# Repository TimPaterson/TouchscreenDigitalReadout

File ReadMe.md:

# Smart Touchscreen DRO for Milling Machines
__As seen in this article in [*Servo* magazine](https://www.timpaterson.com/articles/Servo/SmartDroP1_P2.pdf)!__

### Introduction
The Smart DRO is a touchscreen digital readout for milling machines. You 
can see in the photos an installation on a Grizzly mill/drill, replacing 
the original display head (shown on the mill table). The OEM position 
sensors for the X, Y, and Z axes directly connect to the back of the unit.
Position sensors like these are individually available commercially for 
mills that do not have them factory installed.

The Smart DRO can greatly simplify milling from dimensioned drawings. If 
you enter the diameter of the tool it can automatically adjust the
display reading by the tool radius. This allows you to cut at the specified 
dimension without having to add or subtract the radius offset. Note in the 
lower left corner of the main screen (the dark rectangle with a circle on 
each side): you can select which side you're cutting so it knows whether to
add or subtract the cutter radius.

You can enter the diameter of each tool as you use it, but the Smart DRO
can also keep your entire tool library (up to 500 tools) in non-volatile
memory. You can enter the list manually or import it from a flash drive
if you share it with other programs or devices. The Smart DRO will also
calculate feeds and speeds, and it displays the current feed rate when
any of the axes move.

Another helpful feature is the undo list for changes in the origin of any
axis. If you accidently zero out or set a value to the wrong axis, you can
easily recover the origin even if the axis has been moved.

The on-screen calculator allows you to include axis readings in 
calculations, and copy results back to an axis.

### Sensor Compatibility
It is industry standard that position sensors use a 9-pin "D" connector
(like a PC serial port). However, there is no standard for the pin
assignments for the connector! To solve this, the Smart DRO uses a pinout
adapter for each axis. A tiny printed circuit board with a single connector
routes signals to the correct pins. A set of 3 of these PCBs costs just 45 cents.
See the [*Servo* magazine article](https://www.timpaterson.com/articles/Servo/SmartDroP1_P2.pdf)
for more info.

### The Project
The main component is the 10" LCD touchscreen, specified in the parts 
list. This repository includes all other aspects of the hardware design 
needed to build this project as shown. These elements include:
- Custom [electronics design](https://github.com/TimPaterson/TouchscreenDigitalReadout/tree/master/Electronics),
with printed circuit board ready for fabrication.
- Enclosure design, using a 3D-printed bezel and machined aluminum back.

A [separate repository](https://github.com/TimPaterson/Touchscreen-DRO-Firmware) 
has the microcontroller firmware and graphics images.

Here are the critical links:
- The [*Servo* magazine article](https://www.timpaterson.com/articles/Servo/SmartDroP1_P2.pdf)
has complete instructions on how to build it.
- The [Touchscreen-DRO-Firmware](https://github.com/TimPaterson/Touchscreen-DRO-Firmware) repository
has firmware and everything else you need, bundled into a release.
- [Touchscreen at BuyDisplay.com](https://www.buydisplay.com/serial-spi-i2c-10-1-inch-tft-lcd-module-dislay-w-ra8876-optl-touch-panel).
Be sure to select options per the [parts list](https://github.com/TimPaterson/TouchscreenDigitalReadout/blob/master/Electronics/DroPartsList.pdf).
- [Main PCB shared at OSH Park](https://oshpark.com/shared_projects/AQX5MSFg). The
EAGLE CAD for the PCB is included is you want to use another PCB source.
- Pinout PCBs at OSH Park. Pinouts are specified by a 4-digit number where
the digits are the pin numbers on the 9-pin D-connector for GND, +5V, A, & B, respectively.
  - [2768 (Grizzly)](https://oshpark.com/shared_projects/TLEyl9I6)
  - [2134 (Jing/Jcgs)](https://oshpark.com/shared_projects/ilViDS0E)
  - [6724 (Acu-Rite)](https://oshpark.com/shared_projects/GIDBOB83)
- [Tool Library Manager](https://github.com/TimPaterson/CNC-Tool-Library-Manager)
for making tool libary files the Smart DRO can import.

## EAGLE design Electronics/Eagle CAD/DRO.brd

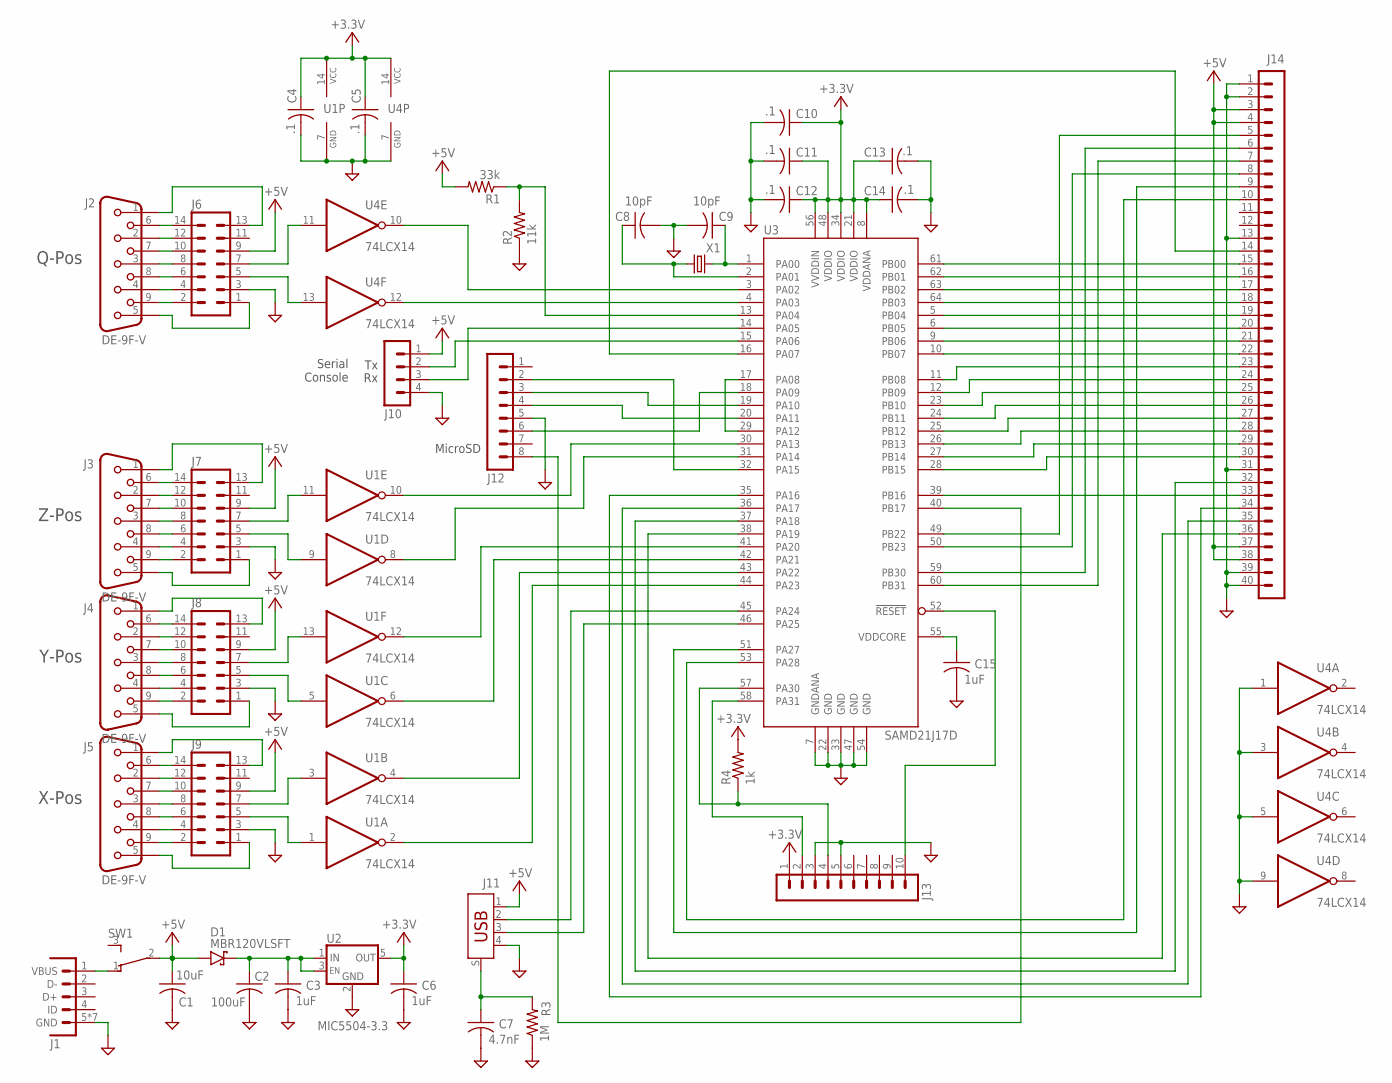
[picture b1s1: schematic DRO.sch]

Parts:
C1: 10uF; 0603
C2: 100uF; C1206
C3, C6, C15: 1uF; 0603
C4, C5, C10, C11, C12, C13, C14: .1; 0603
C7: 4.7nF; 0603
C8, C9: 10pF; 0603
D1: MBR120VLSFT; SOD123
J1: USB_MINI-B-MICRO-B_FCI; USB_MICRO-B_FCI
J2, J3, J4, J5: DE-9F-V; DE-9F-PCB-VERT
J6, J7, J8, J9: CONN-14-BIDI; CONN-1.27X2-14
J10: CONN-4-2.54X1-RA; CONN-2.54X1-4-RA
J11: USB-A-SHIELD; USB-A
J12: CONN-8-2.54X2; CONN-2.54X2-8
J13: CONN-10-ARM; CONN-1.27X2-10
J14: CONN-40; CONN-2.54X2-40
R1: 33k; 0603
R2: 11k; 0603
R3: 1M; 0603
R4: 1k; 0603
SW1: SWITCH-SPDT-MINI-RA-SHORT
U1, U4: 74LCX14; TSSOP14
U2: MIC5504-3.3; SOT23-5
U3: SAMD21J17D; TQFP64-0.5
X1: CRYSTAL-3X1.5; XTAL-SMD-3.2X1.5-2PIN

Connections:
+3.3V: C4.1, C5.1, C6.1, C10.1, C11.1, C12.1, C13.1, C14.1, J13.1, R4.2, U1.14 (VCC), U2.5 (OUT), U3.8 (VDDANA), U3.21 (VDDIO), U3.34 (VDDIO), U3.48 (VDDIO), U3.56 (VVDDIN), U4.14 (VCC)
+5V: C1.1, D1.A, J6.9, J7.9, J8.9, J9.9, J10.1, J11.1, J14.3, J14.4, J14.37, J14.38, R1.2, SW1.2 (C)
GND: C1.2, C2.2, C3.2, C4.2, C5.2, C6.2, C7.2, C8.2, C9.2, C10.2, C11.2, C12.2, C13.2, C14.2, C15.2, J1.5 (GND), J1.SHELL1 (GND), J1.SHELL2 (GND), J1.SHELL3 (GND), J1.SHELL4 (GND), J1.SHELL5 (GND), J1.SHELL6 (GND), J6.3, J7.3, J8.3, J9.3, J10.4, J11.4, J12.5, J13.3, J13.5, J14.1, J14.2, J14.13, J14.31, J14.39, J14.40, R2.1, R3.1, U1.7 (GND), U2.2 (GND), U3.7 (GNDANA), U3.22 (GND), U3.33 (GND), U3.47 (GND), U3.54 (GND), U4.1 (I), U4.3 (I), U4.5 (I), U4.7 (GND), U4.9 (I)
J1: J14.17, U3.63 (PB02)
unnamed: J14.15, U3.61 (PB00)
unnamed: J14.22, U3.10 (PB07)
unnamed: J14.23, U3.11 (PB08)
unnamed: J14.24, U3.12 (PB09)
unnamed: J14.25, U3.23 (PB10)
unnamed: J14.26, U3.24 (PB11)
unnamed: J14.27, U3.25 (PB12)
unnamed: J14.28, U3.26 (PB13)
unnamed: J14.29, U3.27 (PB14)
unnamed: J14.30, U3.28 (PB15)
unnamed: J14.16, U3.62 (PB01)
unnamed: J11.2, U3.45 (PA24)
unnamed: J14.18, U3.64 (PB03)
unnamed: J14.19, U3.5 (PB04)
unnamed: J14.20, U3.6 (PB05)
unnamed: J14.21, U3.9 (PB06)
unnamed: J11.3, U3.46 (PA25)
unnamed: U3.17 (PA08), U3.29 (PA12)
unnamed: R1.1, R2.2, U3.13 (PA04)
unnamed: C9.1, U3.1 (PA00), X1.2
unnamed: C8.1, U3.2 (PA01), X1.1
unnamed: C2.1, C3.1, D1.C, U2.1 (IN), U2.3 (EN)
unnamed: J13.2, U3.58 (PA31)
unnamed: C15.1, U3.55 (VDDCORE)
unnamed: J13.4, R4.1, U3.57 (PA30)
unnamed: J14.33, U3.39 (PB16)
unnamed: J13.10, U3.52 (!RESET)
unnamed: J14.5, U3.49 (PB22)
unnamed: J14.8, U3.50 (PB23)
unnamed: J14.6, U3.59 (PB30)
unnamed: J14.7, U3.60 (PB31)
unnamed: J14.10, U3.53 (PA28)
unnamed: J14.9, U3.51 (PA27)
unnamed: J14.36, U3.38 (PA19)
unnamed: J14.32, U3.37 (PA18)
unnamed: J14.35, U3.36 (PA17)
unnamed: J14.34, U3.35 (PA16)
unnamed: J12.3, U3.19 (PA10)
unnamed: J14.14, U3.16 (PA07)
unnamed: J12.6, U3.18 (PA09)
unnamed: J12.4, U3.20 (PA11)
unnamed: J12.2, U3.32 (PA15)
unnamed: U1.10 (O), U3.30 (PA13)
unnamed: J10.3, U3.14 (PA05)
unnamed: J10.2, U3.15 (PA06)
unnamed: U3.4 (PA03), U4.12 (O)
unnamed: U3.3 (PA02), U4.10 (O)
unnamed: J12.8, U3.40 (PB17)
unnamed: U1.8 (O), U3.31 (PA14)
unnamed: U1.2 (O), U3.44 (PA23)
unnamed: U1.4 (O), U3.43 (PA22)
unnamed: U1.6 (O), U3.42 (PA21)
unnamed: U1.12 (O), U3.41 (PA20)
unnamed: J6.7, U4.11 (I)
unnamed: J6.5, U4.13 (I)
unnamed: J2.5, J6.1
unnamed: J2.9, J6.2
unnamed: J2.4, J6.4
unnamed: J2.8, J6.6
unnamed: J2.3, J6.8
unnamed: J2.7, J6.10
unnamed: J2.2, J6.12
unnamed: J2.6, J6.14
unnamed: J2.1, J6.13
unnamed: J7.5, U1.9 (I)
unnamed: J8.5, U1.5 (I)
unnamed: J9.5, U1.1 (I)
unnamed: J9.7, U1.3 (I)
unnamed: J8.7, U1.13 (I)
unnamed: J7.7, U1.11 (I)
unnamed: J3.6, J7.14
unnamed: J3.2, J7.12
unnamed: J3.7, J7.10
unnamed: J3.3, J7.8
unnamed: J3.8, J7.6
unnamed: J3.4, J7.4
unnamed: J3.9, J7.2
unnamed: J4.6, J8.14
unnamed: J4.2, J8.12
unnamed: J4.7, J8.10
unnamed: J4.3, J8.8
unnamed: J4.8, J8.6
unnamed: J4.4, J8.4
unnamed: J4.9, J8.2
unnamed: J5.6, J9.14
unnamed: J5.2, J9.12
unnamed: J5.7, J9.10
unnamed: J5.3, J9.8
unnamed: J5.8, J9.6
unnamed: J5.4, J9.4
unnamed: J5.9, J9.2
unnamed: J3.1, J7.13
unnamed: J3.5, J7.1
unnamed: J4.1, J8.13
unnamed: J5.1, J9.13
unnamed: J4.5, J8.1
unnamed: J5.5, J9.1
unnamed: C7.1, J11.S (SHIELD), R3.2
VBUS: J1.1 (VBUS), SW1.1 (NC)

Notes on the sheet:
Serial Console
MicroSD
Q-Pos
Z-Pos
Y-Pos
X-Pos

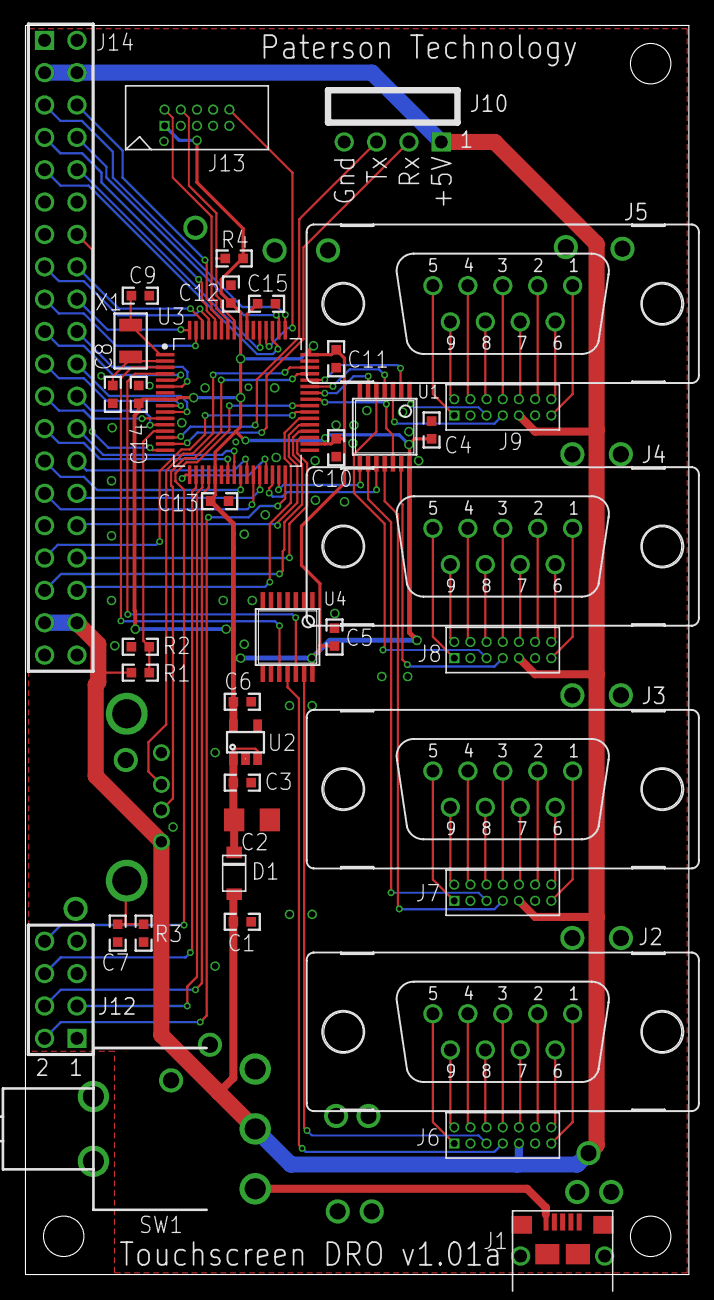
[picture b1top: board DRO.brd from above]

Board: 2 copper layers, 52.1 x 98.0 mm, 40 parts (1 on the bottom side), 103 nets.

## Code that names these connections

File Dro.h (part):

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//*********************************************************************
// Define port pins
//
// PA00 - xtal
// PA01 - xtal
// PA02 - in, Q position A (EXINT 2)
// PA03 - in, Q position B (EXINT 3)
// PA04 - analog in, supply voltage (AC AIN[0])
// PA05 - in, console serial RX data (SERCOM 0 pad 1)
// PA06 - out, console serial TX data (SERCOM 0 pad 2)
// PA07 - out, backlight PWM (TCC1 WO[1])
// PA08 - in, supply low (NMI)
// PA09 - in, MicroSD DOUT/MISO (SERCOM 2 pad 1 & EXINT 9)
// PA10 - out, MicroSD DIN/MOSI (SERCOM 2 pad 2)
// PA11 - out, MicroSD SCK (SERCOM 2 pad 3)
// PA12 - out, supply low (analog comparator CMP[0])
// PA13 - in, Z position A (EXINT 13)
// PA14 - in, Z position B (EXINT 14)
// PA15 - out, MicroSD CS
// PA16 - out, RTP DIN/MOSI (SERCOM 1 pad 0)
// PA17 - out, RTP SCK (SERCOM 1 pad 1)
// PA18 - out, RTP CS
// PA19 - in, RTP DOUT/MISO (SERCOM 1 pad 3)
// PA20 - in, Y position A (EXINT 4)
// PA21 - in, Y position B (EXINT 5)
// PA22 - in, X position A (EXINT 6)
// PA23 - in, X position B (EXINT 7)
// PA24 - USB D-
// PA25 - USB D+
// PA27 - in, RA8876 WAIT (EXINT 15)
// PA28 - in, RA8876 INT (EXINT 8)
//
// PB00 - in/out, RA8876 DB0
// PB01 - in/out, RA8876 DB1
// PB02 - in/out, RA8876 DB2
// PB03 - in/out, RA8876 DB3
// PB04 - in/out, RA8876 DB4
// PB05 - in/out, RA8876 DB5
// PB06 - in/out, RA8876 DB6
// PB07 - in/out, RA8876 DB7
// PB08 - in/out, RA8876 DB8
// PB09 - in/out, RA8876 DB9
// PB10 - in/out, RA8876 DB10
// PB11 - in/out, RA8876 DB11
// PB12 - in/out, RA8876 DB12
// PB13 - in/out, RA8876 DB13
// PB14 - in/out, RA8876 DB14
// PB15 - in/out, RA8876 DB15
// PB16 - in w/pull-up, RTP IRQ (EXINT 0)
// PB17 - in, MicroSD card detect (EXINT 1)
// PB22 - out, RA8876 E (TC7 WO[0])
// PB23 - out, RA8876 C/D
// PB30 - out, RA8877 R/W
// PB31 - out, RA9977 CS

enum PortAbitMap
{
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
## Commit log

2020-10-15 Successfully read mill position sensor
2020-10-18 LCD controller initialization partially complete
2020-10-18 remove .vs folder
2020-10-21 LCD test pattern displays, touch data working
2020-10-23 Success drawing rectangle and display text w/internal font
2020-10-23 Success writing text with external font
2020-10-25 Program serial flash through SPI
2020-10-26 Use printf() to write text to LCD
2020-10-27 Touch logic now reporting screen coordinates
2020-10-28 Target cursor follows touch
2020-11-07 Display keypad and detect touching its keys
2020-11-08 USB mouse working
2020-11-12 Add FAT file system with SD card driver, untested
2020-11-18 FAT file system successfully enumerates root folder on SD card
2020-11-19 Enable parameters to be stored in EEPROM
2020-11-23 Add touch screen calibration, saving result to EEPROM
2020-11-24 Successfully display full screen image from microSD card
2020-12-01 Canvas & TextDisplay classes; success writing string to screen with generated font.
2020-12-15 Main screen image now copied from serial flash
2020-12-17 Text output working again
2020-12-17 TextField and new TextLine support printf
2020-12-18 Get PIP working
2020-12-20 All axis displays show correct position.
2020-12-23 add & implement abs/inc and inch/mm toggle buttons
2020-12-24 add functions to add/remove selection borders
2020-12-26 Figure out text cursor
2020-12-29 Calculator keypad seems fully functional
2020-12-31 Use colors exported by Screen Designer
2021-01-04 Success with display directory and file read on USB flash drive
2021-01-05 Automatically mount SD card or USB flash drive when present
2021-01-07 Implement calculator memories
2021-01-08 Add mouse pointer image; mouse functions same as touch
2021-01-13 Add tool offset and speed/feed display to screen and implement in code
2021-01-19 Create and fully implement settings screen
2021-01-20 Add choice of two orientations of coordinate system
2021-01-20 Save Settings to EEPROM on exit
2021-01-21 Fix PIP hit testing; separate width from stride
2021-01-26 Successful test of list scrolling
2021-01-28 +/- key operates on current value
2021-01-30 Add and display tool library image
2021-01-30 Use image arrays to select image from list
2021-01-31 Refactor tool display, adding ToolLib.h
2021-02-02 ToolLib now handles single tool display
2021-02-04 Manual entry into tool library working
2021-02-06 Final keyboard layouts; import tool library from flash drive
2021-02-07 More tool library functionality: select from list, delete
2021-02-07 Use references instead of pointers on TextField constructors
2021-02-11 Enter/edit tool description w/on-screen keyboard
2021-02-19 Successfully browsing flash drive with list box
2021-02-19 Add Hard Fault handler in Debug mode
2021-02-19 Switch to 16-bit fonts
2021-02-23 Tool library import/export dialog mostly working
2021-02-25 Real-time clock and file timestamps working
2021-02-25 Reorganize ArmLib & Dro folder structures
2021-02-28 Error handling for tool library file operations
2021-02-28 Use image for scroll thumb
2021-03-02 Finish multi-drive support and file error handling
2021-03-02 Add horizontal scrolling to EditLine
2021-03-03 USB keyboard can enter data into edit box
2021-03-04 Add icon to delete content of edit box
2021-03-07 Add touch calibration screen and rework touch calculations
2021-03-12 Build UI for firmware update
2021-03-13 Update graphics & fonts from update file with progress bar
2021-03-14 Restructure LCD graphics classes to derive from implementation-defined base class
2021-03-15 Self-update working
2021-03-15 Display current feed rate
2021-03-16 Make some members of ToolLib instance instead of static
2021-03-17 Implement multi-level undo for each axis
2021-03-18 Fix calculator display for large & small values.
2021-03-18 Save axis positions & clock on power down, restore on startup
2021-03-19 Tool library now kept in flash memory
2021-03-22 Touch-ups
2021-03-22 Use 3-point touch calibration
2021-03-25 Enable NMI last during init
2021-04-05 Update fix, color change
2021-04-23 Tweaks to fonts and colors
2021-04-27 Revert to GCC 9.3; standardize project file XML formatting
2021-05-23 Fix initial setup of blank unit
2021-05-25 Specify executable location for post-build step
2021-05-25 Squashed 'ArmLib/' content from commit 1744b72
    git-subtree-dir: ArmLib
    git-subtree-split: 1744b724ac953cb60116c5ef2f4c61a2181398e2
2021-05-25 Squashed 'DroUpdateBuilder/' content from commit a1ad5c9
    git-subtree-dir: DroUpdateBuilder
    git-subtree-split: a1ad5c94db951d508486e1703e58854436c1d789
2021-05-27 add all project files
2021-07-18 add ReadMe with initial photos
2021-08-08 Adjust certain holes sizes in PCB designs
2021-11-22 Revise initialization for change to ArmLib
2021-11-24 Enable Q input to add quill to column/knee for total Z
2021-11-24 Squashed 'ArmLib/' changes from 1744b72..6003bf1
    6003bf1 Add support for SAM 3/SAM 4
    90fe42b Improve accuracy of ShortDelay() in TimerLib
    1a0828c resolve interference between SetPortMux() and SetPortConfig()
    e68fe99 Make interrupts optional for DMA
    git-subtree-dir: ArmLib
    git-subtree-split: 6003bf13b35d386b4e0ccba8bcb133a540c0b381
2021-11-24 DRO firmware v.2: Enable Q input to add quill to column/knee for total Z
2023-10-24 Firmware split into separate repository
